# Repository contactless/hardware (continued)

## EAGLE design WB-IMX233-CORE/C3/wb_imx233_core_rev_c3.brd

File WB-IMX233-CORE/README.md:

(c) 2013, 2014 Contactless Devices, LLC

WB-IMX233-CORE design is based on Olimex's IMX233-OLINUXINO-MICRO (http://www.olimex.com)

The modifications were made. This derivative work is thereby released under the 
Creative Commons Attribution-Share Alike 3.0 United States License.

You may reproduce it for both your own personal use, and for commertial use.
You will have to provide a link to the original creator of the project on any documentation or website.
You may also modify the files, but you must then release them as well under the same terms.

Credit can be attributed through a link to the creator website: http://contactless.ru.

Original license is as follows:

The Hardware project is released under the Creative Commons Attribution-Share Alike 3.0 United States License.
You may reproduce it for both your own personal use, and for commertial use. 
You will have to provide a link to the original creator of the project http://www.olimex.com on any documentation or website.
You may also modify the files, but you must then release them as well under the same terms.
Credit can be attributed through a link to the creator website: http://www.olimex.com

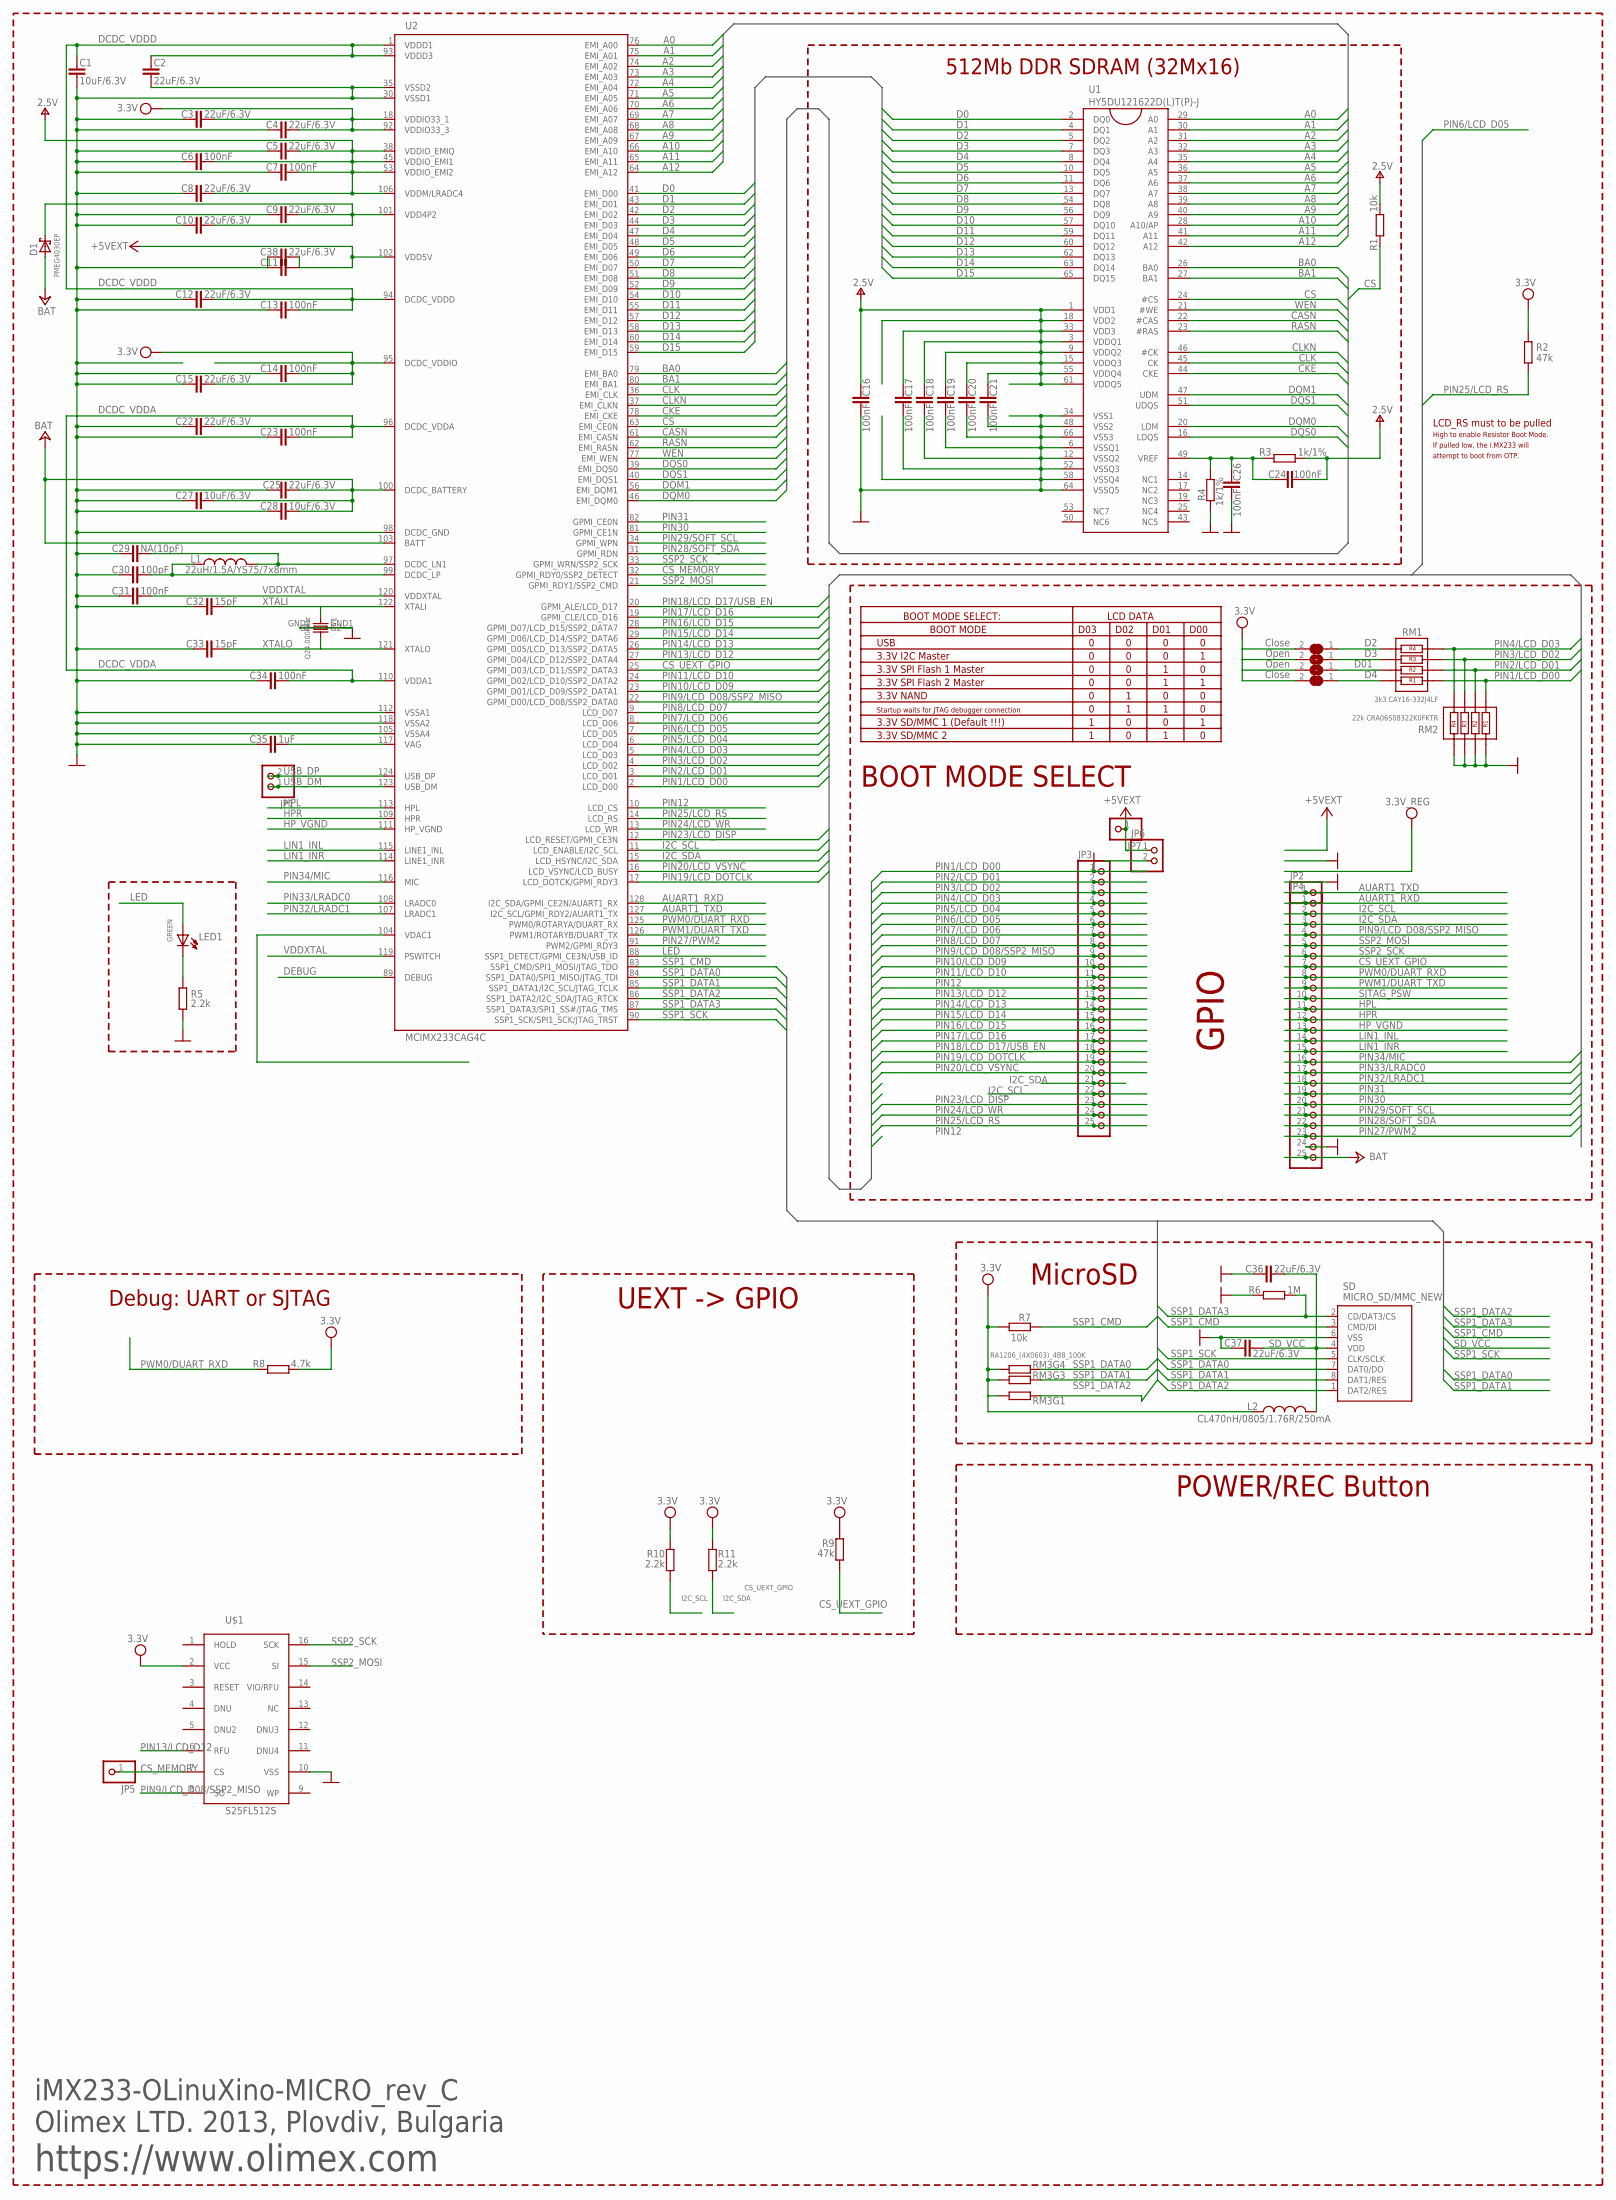
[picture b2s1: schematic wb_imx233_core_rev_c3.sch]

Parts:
C1, C27, C28: 10uF/6.3V; C0603_DWS
C2, C3, C4, C5, C8, C9, C10, C12, C15, C22, C25, C36, C37, C38: 22uF/6.3V; C0603_DWS
C6, C7, C11, C13, C14, C16, C17, C18, C19, C20, C21, C23, C24, C26, C31, C34: 100nF; C0603_DWS
C29: NA(10pF); C0603_DWS
C30: 100pF; C0603_DWS
C32, C33: 15pF; C0603_DWS
C35: 1uF; C0603_DWS
D1: PMEG4030EP; MLL-41
D01_, D3: Open; SJ_1_SMALLER
D2, D4: Close; SJ_1_SMALLER
JP1, JP6: PINHD-1X2; 1X02-R
JP2, JP5, JP7: PINHD-1X1; 1X01
JP3, JP4: PINHD-1X25; 1X25
L1: 22uH/1.5A/YS75/7x8mm; L7078
L2: CL470nH/0805/1.76R/250mA; L0805_5MIL_DWS
LED1: GREEN; LED-0805
R1, R7: 10k; R0603_5MIL_DWS
R2, R9: 47k; R0603_5MIL_DWS
R3, R4: 1k/1%; R0603_5MIL_DWS
R5, R10, R11: 2.2k; R0603_5MIL_DWS
R6: 1M; R0603_5MIL_DWS
R8: 4.7k; R0603_5MIL_DWS
RM1: 3k3 CAY16-332J4LF; R_MATRIX_4
RM2: 22k CRA06S08322K0FKTR; R_MATRIX_4
RM3: RA1206_(4X0603)_4B8_100K; R_MATRIX_4
SD: MICRO_SD/MMC_NEW; TFR/C-MEM-CON
U1: HY5DU121622D(L)T(P)-J; 66TSOP-II
U2: MCIMX233CAG4C; TQFP128LD
U$1: S25FL512S; 1
Y1: Q24.000MHz; CRYSTAL_3.2X2.5

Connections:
+5V: C11.2, C38.2, JP6.1, JP7.1, U2.102 (VDD5V)
+24V: C25.2, C27.2, C28.2, D1.A, JP4.25, U2.100 (DCDC_BATTERY), U2.103 (BATT)
A0: U1.29 (A0), U2.76 (EMI_A00)
A1: U1.30 (A1), U2.75 (EMI_A01)
A2: U1.31 (A2), U2.74 (EMI_A02)
A3: U1.32 (A3), U2.73 (EMI_A03)
A4: U1.35 (A4), U2.72 (EMI_A04)
A5: U1.36 (A5), U2.71 (EMI_A05)
A6: U1.37 (A6), U2.70 (EMI_A06)
A7: U1.38 (A7), U2.69 (EMI_A07)
A8: U1.39 (A8), U2.68 (EMI_A08)
A9: U1.40 (A9), U2.67 (EMI_A09)
A10: U1.28 (A10/AP), U2.66 (EMI_A10)
A11: U1.41 (A11), U2.65 (EMI_A11)
A12: U1.42 (A12), U2.64 (EMI_A12)
AUART1_RXD: JP4.1, U2.128 (I2C_SDA/GPMI_CE2N/AUART1_RX)
AUART1_TXD: JP2.1, U2.127 (I2C_SCL/GPMI_RDY2/AUART1_TX)
BA0: U1.26 (BA0), U2.79 (EMI_BA0)
BA1: U1.27 (BA1), U2.80 (EMI_BA1)
CASN: U1.22 (#CAS), U2.61 (EMI_CASN)
CKE: U1.44 (CKE), U2.78 (EMI_CKE)
CLK: U1.45 (CK), U2.36 (EMI_CLK)
CLKN: U1.46 (#CK), U2.37 (EMI_CLKN)
CS: R1.1, U1.24 (#CS), U2.63 (EMI_CE0N)
CS_MEMORY: JP5.1, U2.32 (GPMI_RDY0/SSP2_DETECT), U$1.7 (CS)
CS_UEXT_GPIO: JP4.7, R9.1, U2.25 (GPMI_D03/LCD_D11/SSP2_DATA3)
D0: U1.2 (DQ0), U2.41 (EMI_D00)
D1: U1.4 (DQ1), U2.43 (EMI_D01)
D2: U1.5 (DQ2), U2.42 (EMI_D02)
D3: U1.7 (DQ3), U2.44 (EMI_D03)
D4: U1.8 (DQ4), U2.47 (EMI_D04)
D5: U1.10 (DQ5), U2.48 (EMI_D05)
D6: U1.11 (DQ6), U2.49 (EMI_D06)
D7: U1.13 (DQ7), U2.50 (EMI_D07)
D8: U1.54 (DQ8), U2.51 (EMI_D08)
D9: U1.56 (DQ9), U2.52 (EMI_D09)
D10: U1.57 (DQ10), U2.54 (EMI_D10)
D11: U1.59 (DQ11), U2.55 (EMI_D11)
D12: U1.60 (DQ12), U2.57 (EMI_D12)
D13: U1.62 (DQ13), U2.58 (EMI_D13)
D14: U1.63 (DQ14), U2.60 (EMI_D14)
D15: U1.65 (DQ15), U2.59 (EMI_D15)
DCDC_VDDA: C22.2, C23.2, C34.2, U2.96 (DCDC_VDDA), U2.110 (VDDA1)
DCDC_VDDD: C1.2, C2.2, C12.2, C13.2, U2.1 (VDDD1), U2.93 (VDDD3), U2.94 (DCDC_VDDD)
DEBUG: U2.89 (DEBUG)
DQM0: U1.20 (LDM), U2.46 (EMI_DQM0)
DQM1: U1.47 (UDM), U2.56 (EMI_DQM1)
DQS0: U1.16 (LDQS), U2.39 (EMI_DQS0)
DQS1: U1.51 (UDQS), U2.40 (EMI_DQS1)
GND: C1.1, C2.1, C3.1, C4.1, C5.1, C6.1, C7.1, C8.1, C9.1, C10.1, C11.1, C12.1, C13.1, C14.1, C15.1, C16.1, C17.1, C18.1, C19.1, C20.1, C21.1, C22.1, C23.1, C25.1, C26.1, C27.1, C28.1, C29.1, C30.1, C31.1, C32.1, C33.1, C34.1, C35.1, C36.1, C37.1, C38.1, JP4.24, JP6.2, R4.1, R5.1, R6.2, RM2.1.2, RM2.2.2, RM2.3.2, RM2.4.2, SD.6 (VSS), U1.6 (VSSQ1), U1.12 (VSSQ2), U1.34 (VSS1), U1.48 (VSS2), U1.52 (VSSQ3), U1.58 (VSSQ4), U1.64 (VSSQ5), U1.66 (VSS3), U2.30 (VSSD1), U2.35 (VSSD2), U2.98 (DCDC_GND), U2.105 (VSSA4), U2.112 (VSSA1), U2.118 (VSSA2), U$1.10 (VSS), Y1.GND1 (G1), Y1.GND2 (G2)
HPL: JP4.11, U2.113 (HPL)
HPR: JP4.12, U2.109 (HPR)
HP_VGND: JP4.13, U2.111 (HP_VGND)
I2C_SCL: JP3.22, JP4.2, R10.1, U2.11 (LCD_ENABLE/I2C_SCL)
I2C_SDA: JP3.21, JP4.3, R11.1, U2.15 (LCD_HSYNC/I2C_SDA)
LED: LED1.A, U2.88 (SSP1_DETECT/GPMI_CE3N/USB_ID)
LIN1_INL: JP4.14, U2.115 (LINE1_INL)
LIN1_INR: JP4.15, U2.114 (LINE1_INR)
unnamed: D2.1, RM1.4.1
unnamed: D3.1, RM1.3.1
unnamed: D01_.1, RM1.2.1
unnamed: D4.1, RM1.1.1
unnamed: C24.2, C26.2, R3.1, R4.2, U1.49 (VREF)
unnamed: C29.2, L1.2, U2.97 (DCDC_LN1)
unnamed: C30.2, L1.1, U2.99 (DCDC_LP)
unnamed: C35.2, U2.117 (VAG)
unnamed: LED1.C, R5.2
PIN1/LCD_D00: JP3.1, RM1.1.2, RM2.1.1, U2.2 (LCD_D00)
PIN2/LCD_D01: JP3.2, RM1.2.2, RM2.2.1, U2.3 (LCD_D01)
PIN3/LCD_D02: JP3.3, RM1.3.2, RM2.3.1, U2.4 (LCD_D02)
PIN4/LCD_D03: JP3.4, RM1.4.2, RM2.4.1, U2.5 (LCD_D03)
PIN5/LCD_D04: JP3.5, U2.6 (LCD_D04)
PIN6/LCD_D05: JP3.6, U2.7 (LCD_D05)
PIN7/LCD_D06: JP3.7, U2.8 (LCD_D06)
PIN8/LCD_D07: JP3.8, U2.9 (LCD_D07)
PIN9/LCD_D08/SSP2_MISO: JP3.9, JP4.4, U2.22 (GPMI_D00/LCD_D08/SSP2_DATA0), U$1.8 (SO)
PIN10/LCD_D09: JP3.10, U2.23 (GPMI_D01/LCD_D09/SSP2_DATA1)
PIN11/LCD_D10: JP3.11, U2.24 (GPMI_D02/LCD_D10/SSP2_DATA2)
PIN12: JP3.12, U2.10 (LCD_CS)
PIN13/LCD_D12: JP3.13, U2.27 (GPMI_D04/LCD_D12/SSP2_DATA4), U$1.6 (RFU)
PIN14/LCD_D13: JP3.14, U2.26 (GPMI_D05/LCD_D13/SSP2_DATA5)
PIN15/LCD_D14: JP3.15, U2.29 (GPMI_D06/LCD_D14/SSP2_DATA6)
PIN16/LCD_D15: JP3.16, U2.28 (GPMI_D07/LCD_D15/SSP2_DATA7)
PIN17/LCD_D16: JP3.17, U2.19 (GPMI_CLE/LCD_D16)
PIN18/LCD_D17/USB_EN: JP3.18, U2.20 (GPMI_ALE/LCD_D17)
PIN19/LCD_DOTCLK: JP3.19, U2.17 (LCD_DOTCK/GPMI_RDY3)
PIN20/LCD_VSYNC: JP3.20, U2.16 (LCD_VSYNC/LCD_BUSY)
PIN23/LCD_DISP: JP3.23, U2.12 (LCD_RESET/GPMI_CE3N)
PIN24/LCD_WR: JP3.24, U2.13 (LCD_WR)
PIN25/LCD_RS: JP3.25, R2.2, U2.14 (LCD_RS)
PIN27/PWM2: JP4.23, U2.91 (PWM2/GPMI_RDY3)
PIN28/SOFT_SDA: JP4.22, U2.31 (GPMI_RDN)
PIN29/SOFT_SCL: JP4.21, U2.34 (GPMI_WPN)
PIN30: JP4.20, U2.81 (GPMI_CE1N)
PIN31: JP4.19, U2.82 (GPMI_CE0N)
PIN32/LRADC1: JP4.18, U2.107 (LRADC1)
PIN33/LRADC0: JP4.17, U2.108 (LRADC0)
PIN34/MIC: JP4.16, U2.116 (MIC)
PWM0/DUART_RXD: JP4.8, R8.2, U2.125 (PWM0/ROTARYA/DUART_RX)
PWM1/DUART_TXD: JP4.9, U2.126 (PWM1/ROTARYB/DUART_TX)
RASN: U1.23 (#RAS), U2.62 (EMI_RASN)
SD_VCC: C36.2, C37.2, L2.2, SD.4 (VDD)
SJTAG_PSW: JP4.10
SSP1_CMD: R7.1, SD.3 (CMD/DI), U2.83 (SSP1_CMD/SPI1_MOSI/JTAG_TDO)
SSP1_DATA0: RM3.4.1 (1), SD.7 (DAT0/DO), U2.84 (SSP1_DATA0/SPI1_MISO/JTAG_TDI)
SSP1_DATA1: RM3.3.1 (1), SD.8 (DAT1/RES), U2.85 (SSP1_DATA1/I2C_SCL/JTAG_TCLK)
SSP1_DATA2: RM3.1.1 (1), SD.1 (DAT2/RES), U2.86 (SSP1_DATA2/I2C_SDA/JTAG_RTCK)
SSP1_DATA3: R6.1, SD.2 (CD/DAT3/CS), U2.87 (SSP1_DATA3/SPI1_SS#/JTAG_TMS)
SSP1_SCK: SD.5 (CLK/SCLK), U2.90 (SSP1_SCK/SPI1_SCK/JTAG_TRST)
SSP2_MOSI: JP4.5, U2.21 (GPMI_RDY1/SSP2_CMD), U$1.15 (SI)
SSP2_SCK: JP4.6, U2.33 (GPMI_WRN/SSP2_SCK), U$1.16 (SCK)
USB_DM: JP1.1, U2.123 (USB_DM)
USB_DP: JP1.2, U2.124 (USB_DP)
V+: C5.2, C6.2, C7.2, C8.2, C16.2, C17.2, C18.2, C19.2, C20.2, C21.2, C24.1, R1.2, R3.2, U1.1 (VDD1), U1.3 (VDDQ1), U1.9 (VDDQ2), U1.15 (VDDQ3), U1.18 (VDD2), U1.33 (VDD3), U1.55 (VDDQ4), U1.61 (VDDQ5), U2.38 (VDDIO_EMIQ), U2.45 (VDDIO_EMI1), U2.53 (VDDIO_EMI2), U2.106 (VDDM/LRADC4)
VCC: C3.2, C4.2, C14.2, C15.2, D01_.2, D2.2, D3.2, D4.2, L2.1, R2.1, R7.2, R8.1, R9.2, R10.2, R11.2, RM3.1.2 (2), RM3.3.2 (2), RM3.4.2 (2), U2.18 (VDDIO33_1), U2.92 (VDDIO33_3), U2.95 (DCDC_VDDIO), U$1.2 (VCC)
VDAC1: U2.104 (VDAC1)
VDD4P2: C9.2, C10.2, D1.K (C), U2.101 (VDD4P2)
VDDXTAL: C31.2, U2.119 (PSWITCH), U2.120 (VDDXTAL)
WEN: U1.21 (#WE), U2.77 (EMI_WEN)
XTALI: C32.2, U2.122 (XTALI), Y1.1
XTALO: C33.2, U2.121 (XTALO), Y1.2

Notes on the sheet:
512Mb DDR SDRAM (32Mx16)
MicroSD
POWER/REC Button
BOOT MODE SELECT
UEXT -> GPIO
BOOT MODE SELECT:
LCD DATA
BOOT MODE
D03
D02
D01
D00
USB
3.3V I2C Master
3.3V SPI Flash 1 Master
3.3V SPI Flash 2 Master
3.3V NAND
Startup waits for JTAG debugger connection
3.3V SD/MMC 1 (Default !!!)
3.3V SD/MMC 2
LCD_RS must to be pulled
High to enable Resistor Boot Mode.
If pulled low, the i.MX233 will
attempt to boot from OTP.
GPIO
Debug: UART or SJTAG
iMX233-OLinuXino-MICRO_rev_C
Olimex LTD. 2013, Plovdiv, Bulgaria
https://www.olimex.com

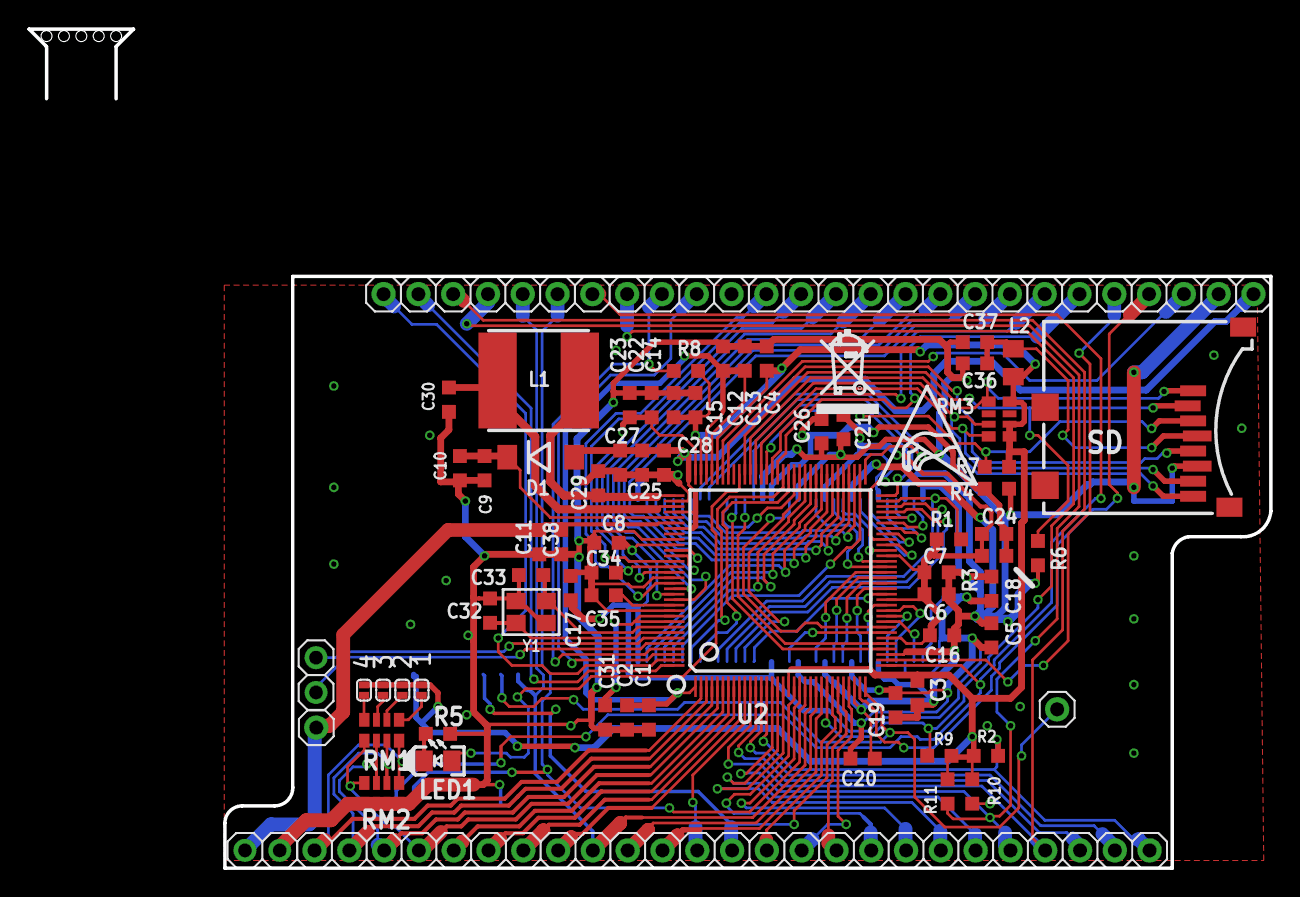
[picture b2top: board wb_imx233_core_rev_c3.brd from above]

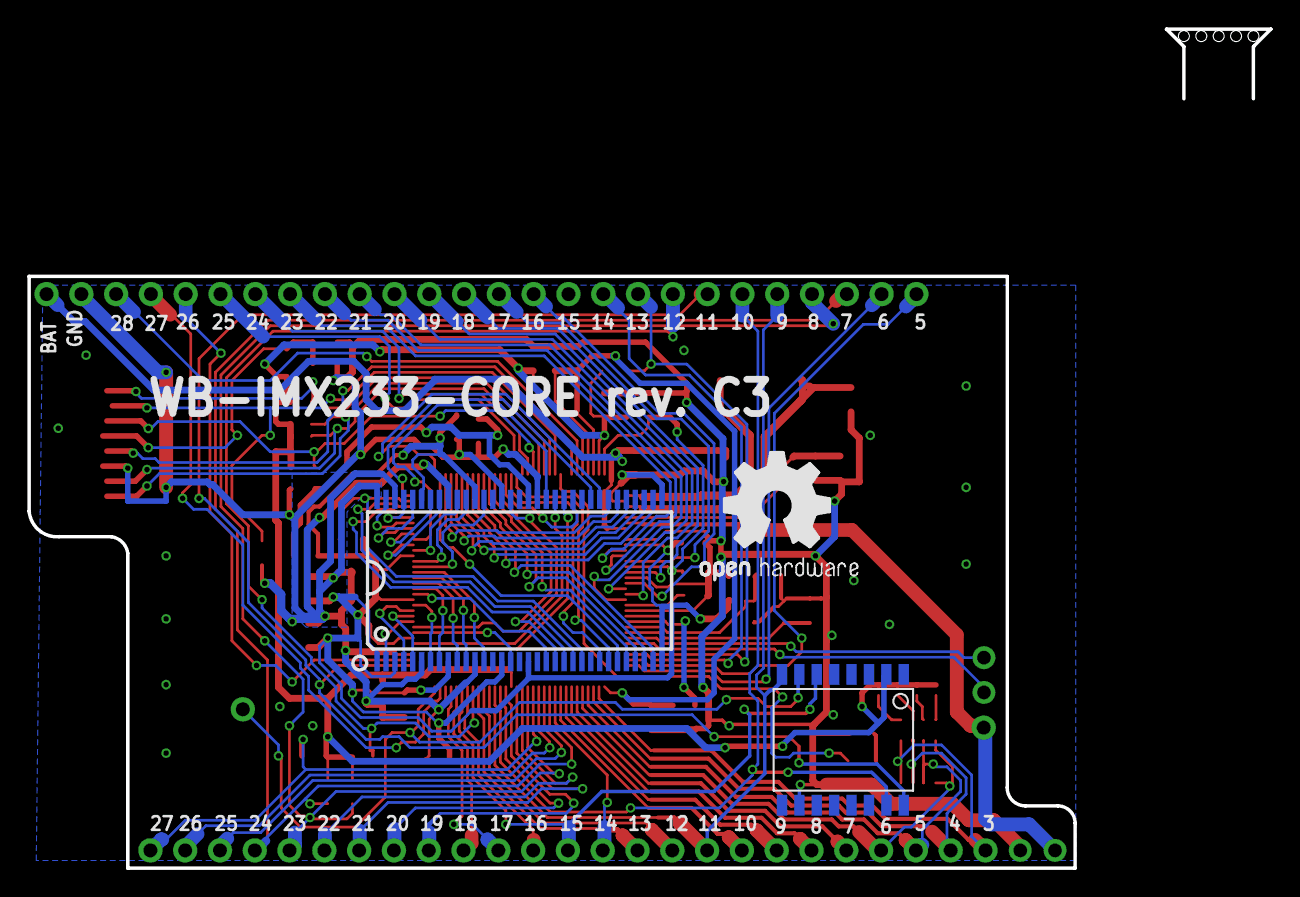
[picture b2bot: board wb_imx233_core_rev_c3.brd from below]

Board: 2 copper layers, 76.4 x 43.2 mm, 75 parts (3 on the bottom side), 118 nets.

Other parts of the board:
U$5: LOGO-OPENHARDWARE_8X8
U$10: ESD_SYMBOL
U$11: RECYCLE_BIN1/8

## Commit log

2014-07-02 add WB-IMX233-CORE rev. C3
2014-07-02 minor readme fix
2016-03-22 Add WB2.8
2016-03-22 add (c)
2016-03-22 add wb4 and wb3.5
2016-03-22 add wb5
